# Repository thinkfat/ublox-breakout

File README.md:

ublox-breakout
==============

This is a breakout board for LEA (and eventually NEO) M8 Ublox GNSS modules.
Its main features are:
- 12 contact pin header for signals
- Micro USB receptacle
- 5V power supply via USB or pin header
- buffered PPS output with SMA receptacle
- small size 47.2mm x 33.2mm
- support for active GPS antenna with 3.3V bias voltage
- 4 mounting holes for M2.5 screws or stand-offs.
- EDS protection for antenna input
- Clip for CR1220 backup battery

This repository contains a KiCAD 5 project with schematic and PCB. The **fab** folder
contains the Gerber files and also BOM and CPL files for JLCPCB SMT service. If you
order the board, make sure to check "Impedance control" and use the JLC7628 stack-up.

All SMT parts are in JLCPCBs SMT library, except for the USB receptacle, battery clip and
antenna input ESD protection diode.
- USB: Molex 47346-0001
- Battery clip: Keystone 3000
- ESD diode: ONsemi ESD9R3.3ST5G

The mounting hole centers are offset 3mm from the board edges.

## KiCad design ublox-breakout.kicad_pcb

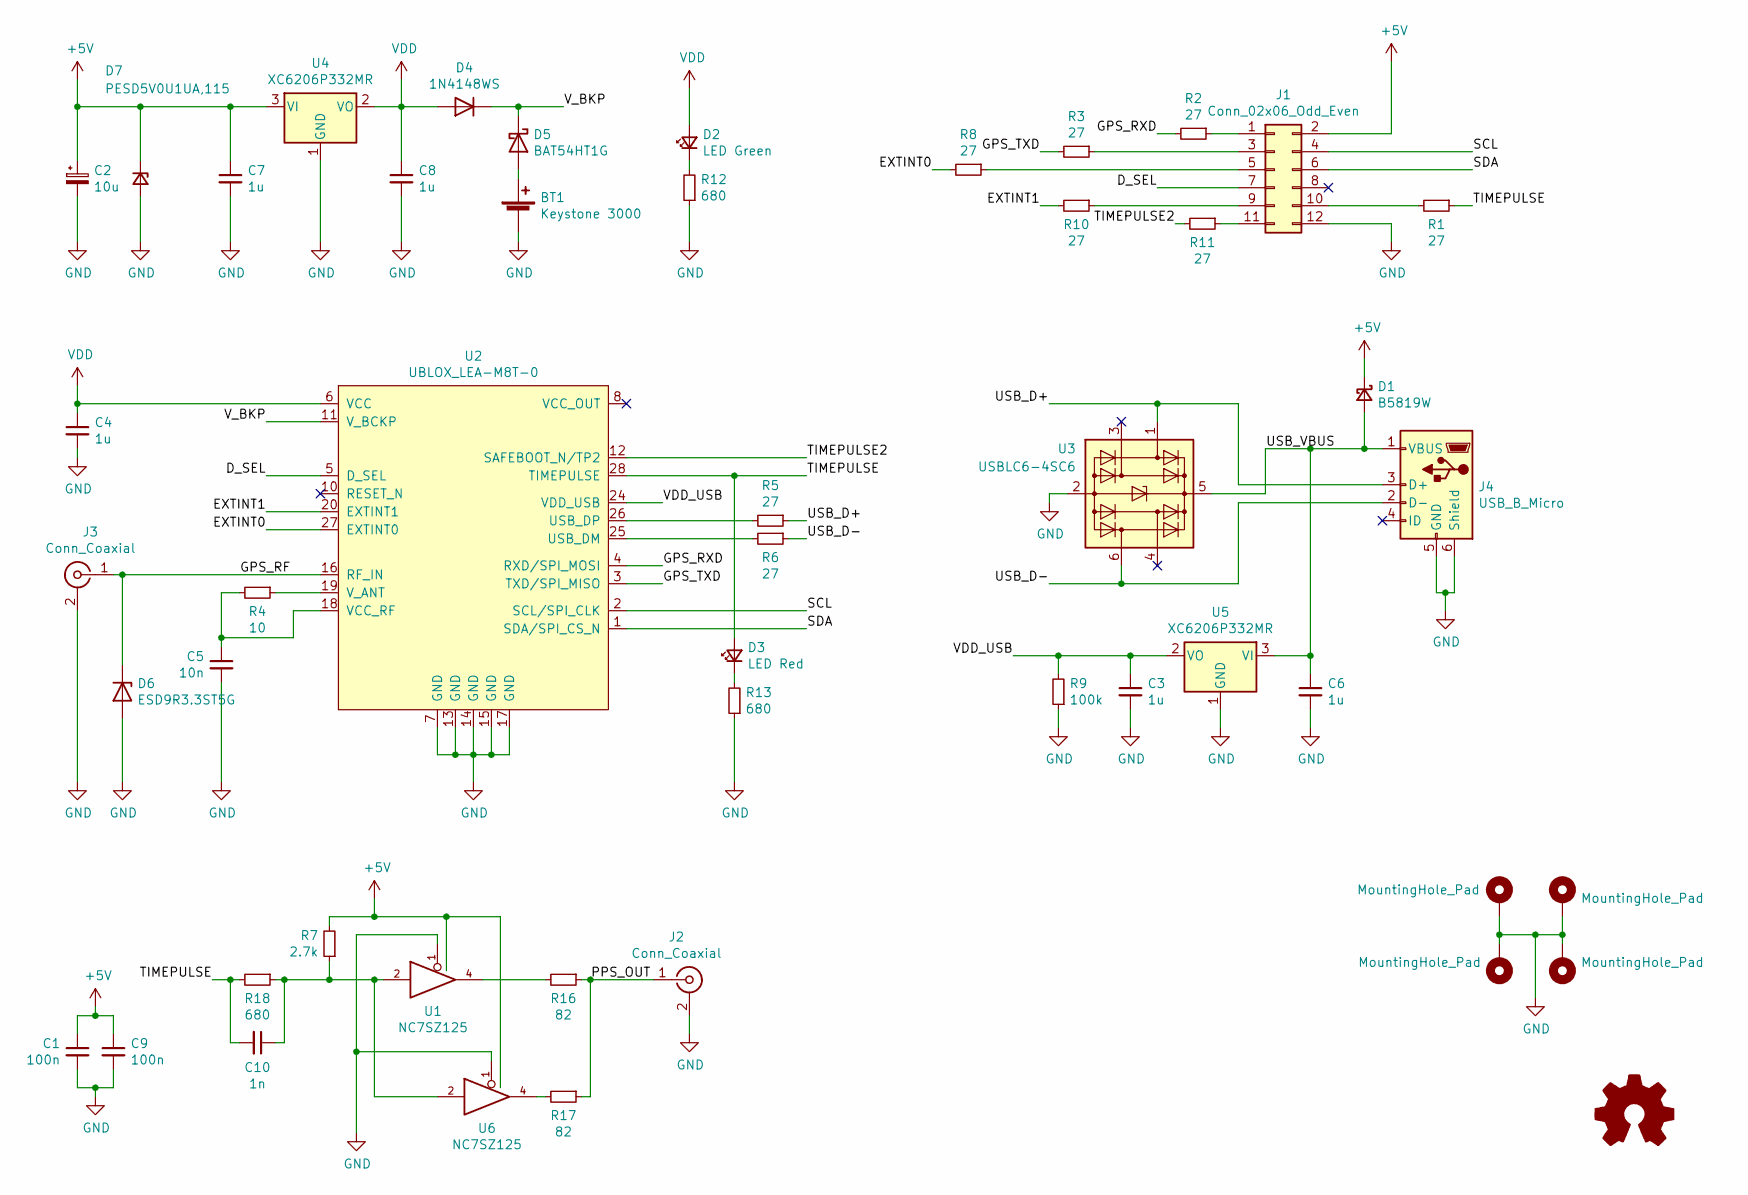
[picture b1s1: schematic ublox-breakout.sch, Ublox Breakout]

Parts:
BT1: Keystone 3000; BatteryHolder_Keystone_3000_1x12mm
C1, C9: 100n; C_0603_1608Metric; JLCPN C14663
C2: 10u; CP_EIA-3216-18_Kemet-A; JLCPN C7171
C3, C4, C6, C7, C8: 1u; C_0603_1608Metric; JLCPN C29936
C5: 10n; C_0603_1608Metric; MPN 0603B103K500NT; JLCPN C57112
C10: 1n; C_0603_1608Metric; JLCPN C1588
D1: B5819W; D_SOD-123; MPN B5819W; JLCPN C8598
D2: LED Green; LED_0603_1608Metric; JLCPN C72043
D3: LED Red; LED_0603_1608Metric; JLCPN C2286
D4: 1N4148WS; D_SOD-323; JLCPN C2128
D5: BAT54HT1G; D_SOD-323; JLCPN C21107
D6: ESD9R3.3ST5G; D_SOD-923
D7: PESD5V0U1UA,115; D_SOD-323; JLCPN C139614
H1, H2, H3, H4: MountingHole_Pad; MountingHole_2.2mm_M2_Pad_Via
J1: Conn_02x06_Odd_Even; PinHeader_2x06_P2.54mm_Vertical
J2, J3: Conn_Coaxial; SMA_Amphenol_132134_Vertical
J4: USB_B_Micro; USB_Micro-B_Molex_47346-0001
OSHW1: Logo_Open_Hardware_Small; OSHW-Logo2_9.8x8mm_SilkScreen
R1, R2, R3, R5, R6, R8, R10, R11: 27; R_0603_1608Metric; JLCPN C25190
R4: 10; R_0603_1608Metric; JLCPN C22859
R7: 2.7k; R_0603_1608Metric; JLCPN C13167
R9: 100k; R_0603_1608Metric; JLCPN C25803
R12, R13, R18: 680; R_0603_1608Metric; JLCPN C23228
R16, R17: 82; R_0603_1608Metric; JLCPN C23255
U1, U6: NC7SZ125; SOT-353_SC-70-5; JLCPN C112084
U2: UBLOX_LEA-M8T-0; ublox_LEA
U3: USBLC6-4SC6; SOT-23-6; JLCPN C111212
U4, U5: XC6206P332MR; SOT-23; JLCPN C5446

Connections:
+5V: C1.1, C2.1, C7.1, C9.1, D1.1 (K), D7.1 (K), J1.2, R7.2, U1.5 (VCC), U4.3 (VI), U6.5 (VCC)
/D_SEL: J1.7, U2.5 (D_SEL)
/EXTINT0: R8.2, U2.27 (EXTINT0)
/EXTINT1: R10.2, U2.20 (EXTINT1)
/GPS_RF: D6.1 (K), J3.1 (In), U2.16 (RF_IN)
/GPS_RXD: R2.2, U2.4 (RXD/SPI_MOSI)
/GPS_TXD: R3.2, U2.3 (TXD/SPI_MISO)
/PPS_OUT: J2.1 (In), R16.1, R17.1
/SCL: J1.4, U2.2 (SCL/SPI_CLK)
/SDA: J1.6, U2.1 (SDA/SPI_CS_N)
/TIMEPULSE: C10.2, D3.2 (A), R1.1, R18.2, U2.28 (TIMEPULSE)
/TIMEPULSE2: R11.2, U2.12 (SAFEBOOT_N/TP2)
/USB_D+: J4.3 (D+), R5.1, U3.1 (I/O1)
/USB_D-: J4.2 (D-), R6.1, U3.6 (I/O4)
/USB_VBUS: C6.1, D1.2 (A), J4.1 (VBUS), U3.5 (VBUS), U5.3 (VI)
/VDD_USB: C3.1, R9.2, U2.24 (VDD_USB), U5.2 (VO)
/V_BKP: D4.1 (K), D5.1 (K), U2.11 (V_BCKP)
GND: BT1.2 (-), C1.2, C2.2, C3.2, C4.2, C5.2, C6.2, C7.2, C8.2, C9.2, D6.2 (A), D7.2 (A), H1.1, H2.1, H3.1, H4.1, J1.12, J2.2 (Ext), J3.2 (Ext), J4.5 (GND), J4.6 (Shield), R9.1, R12.1, R13.1, U1.1, U1.3 (GND), U2.7 (GND), U2.13 (GND), U2.14 (GND), U2.15 (GND), U2.17 (GND), U3.2 (GND), U4.1 (GND), U5.1 (GND), U6.1, U6.3 (GND)
unnamed: BT1.1 (+), D5.2 (A)
unnamed: C5.1, R4.2, U2.18 (VCC_RF)
unnamed: C10.1, R7.1, R18.1, U1.2, U6.2
unnamed: D2.1 (K), R12.2
unnamed: D3.1 (K), R13.2
unnamed: J1.1, R2.1
unnamed: J1.3, R3.1
unnamed: J1.5, R8.1
unnamed: J1.9, R10.1
unnamed: J1.10, R1.2
unnamed: J1.11, R11.1
unnamed: R4.1, U2.19 (V_ANT)
unnamed: R5.2, U2.26 (USB_DP)
unnamed: R6.2, U2.25 (USB_DM)
unnamed: R16.2, U1.4
unnamed: R17.2, U6.4
VDD: C4.1, C8.1, D2.2 (A), D4.2 (A), U2.6 (VCC), U4.2 (VO)

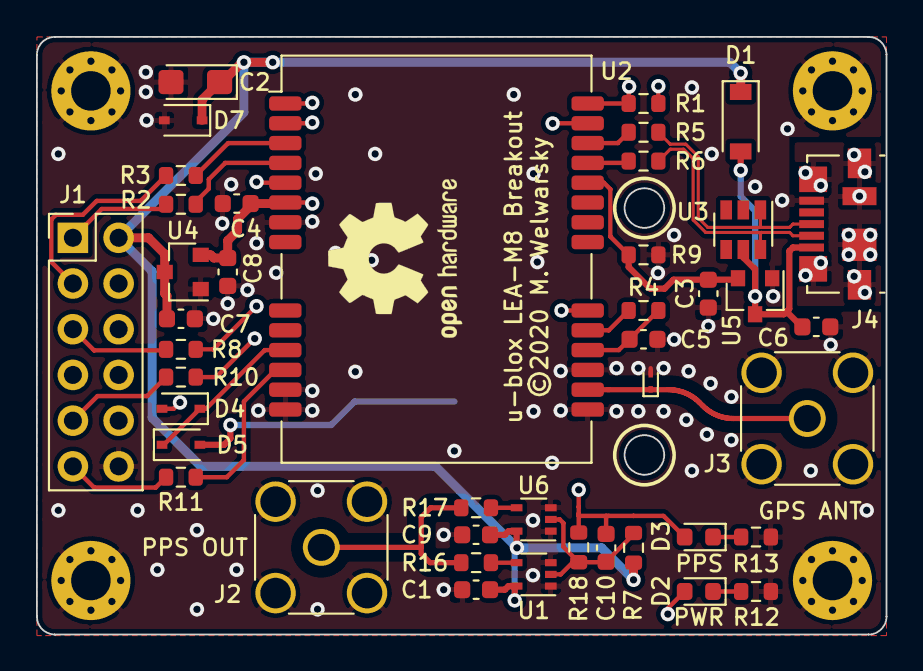
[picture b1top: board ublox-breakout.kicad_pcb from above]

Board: 4 copper layers, 47.2 x 33.2 mm, 49 parts (1 on the bottom side), 35 nets.

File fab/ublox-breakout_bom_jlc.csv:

"Comment","Designator","Footprint","LCSC Part #"
"100n","C1,C9","C_0603_1608Metric","C14663"
"10u","C2","CP_EIA-3216-18_Kemet-A","C7171"
"1u","C4,C6,C7,C8,C3","C_0603_1608Metric","C29936"
"10n","C5","C_0603_1608Metric","C57112"
"1n","C10","C_0603_1608Metric","C1588"
"B5819W","D1","D_SOD-123","C8598"
"LED Green","D2","LED_0603_1608Metric","C72043"
"LED Red","D3","LED_0603_1608Metric","C2286"
"1N4148WS","D4","D_SOD-323","C2128"
"BAT54HT1G","D5","D_SOD-323","C21107"
"PESD5V0U1UA,115","D7","D_SOD-323","C139614"
"27","R2,R3,R1,R5,R6,R10,R11,R8","R_0603_1608Metric","C25190"
"10","R4","R_0603_1608Metric","C22859"
"2.7k","R7","R_0603_1608Metric","C13167"
"100k","R9","R_0603_1608Metric","C25803"
"680","R12,R13,R18","R_0603_1608Metric","C23228"
"82","R16,R17","R_0603_1608Metric","C23255"
"NC7SZ125","U1,U6","SOT-353_SC-70-5","C112084"
"USBLC6-4SC6","U3","SOT-23-6","C111212"
"XC6206P332MR","U4,U5","SOT-23","C5446"

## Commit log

2020-12-10 Initial commit
    Breakout PCB for UBlox M8T GNSS receiver
2020-12-12 Prototype LEA-M8 breakout board
    includes fabrication Gerber files and BOM+CPL files for
    JLCPCB SMT service.
    PCB must be ordered with impedance control JLC7628 stack-up
2020-12-14 Update LEA breakout board:
    - add backup battery
    - add buffered PPS output
    - add pull-up resistors for SCL/SDA
    - add D_SEL on pin header
2020-12-15 Add README
2020-12-15 BOM and schematic updates
    - mark I2C pull-ups DNP (module has built-in pull resistors)
    - small schematic cleanups
    - add schematic PDF and board image
    - update fabrication data
2020-12-15 PCB and schematic updates
    - change backup battery circuit to prevent inverse current
    - add bulk capacitor to +5V rail
    - add ESD protection diode for RF input
2020-12-27 Fix USB and other issues
    - use an LDO to provide VDD_USB as per HIM (major issue)
    - correct trace width for GPS antenna input (minor issue)
    - add OSHW logo on top silk
    - add copyright notice on top silk
    - update gerber, BOM and CPL files
    - update schematic PDF
2021-01-02 USB updates and 1PPS updates
    These changes make the USB ESD protection fully optional since the
    USBLC6-2SC6 is frequently out of stock at JLCPCB
    - replace USBLC6-2SC6 with USBLC6-4SC6
    - route a 7mil/4mil differential pair under its body and connect it
    Tighter coupling of the 74HCT2G125 buffer to the SMA connector to
    bring the impedance closer to 50 Ohm
2021-01-05 Update PPS output buffer
    Change output buffer to 2*NC7SZ125, add a small resistor network
    to lift the input signal from 3.3V LVC to standard 5V CMOS
2021-01-19 Overvoltage and R.P. protection, PPS buffer updates
    Added an ESD diode at the input to protect the bulk
    decoupling capacitor (tantalum). It's unidirectional and provides
    at least some reverse polarity protection as well (will short out).
    Faster rise time at input gate of PPS buffers by adding a small
    10nF capacitor
    Move USB ESD protection a bit to make soldering the USB receptacle

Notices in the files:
ublox-breakout.kicad_pcb:
©2020 M. Welwarsky
